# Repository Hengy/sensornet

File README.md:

SensorNet
-----------------------------------------------

SensorNet is a wireless network optimised for small data transfers that are typical of sensor and automation devices. Where the 802.11 standard (WiFi) is meant for large data streams, networking, etc. - with the overhead that comes with it - Sensornet is optimised for the inherently small data needed for sensors and automation control.

The data requirements of the typical sensor is from 1 bit (open/closed) to 24 bits (8-bit representation of a colour). Automation has similar requirements - from 1 bit (on/off) control, to 36 bits (12-bit PWM control of a RGB light).

Sensornet provides a common API for multiple microcontroller architectures, allowing simple transfer and management of sensor and automation control data, as well as a web-based interface centred around the inexpensive, but powerful Raspberry Pi platform.

Using the SensorNet libraries and templates, rapid development of SensorNet compatible sensors and automation controls is possible in as little as a few hours, while access to advanced features allow for complex, smart devices with advanced functionality.

iPhone App
Two good friends of mine developed an iPhone App for SensorNet. It can be found here: https://github.com/Qblack/SensorNet

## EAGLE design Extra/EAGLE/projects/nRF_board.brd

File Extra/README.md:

Extras
-----------------------------------------------

These are extras that were made during the development of SensorNet, mostly out of necessity.

The Temp Control folder contains a program to self regulate the RPis temperature using a fan. The fan speed is regulated using a PWM signal.

The EAGLE folder contains a PCB design for an interface board for the nRF24L01+. The board includes an optional 3.33v regulator, power LED, and reservoir capacitors. The reservoir capacitors are necessary when using a small microcontroller and a nRF24L01+ with a LNA. The power draw when switching to TX mode may be too much for the microcontroller. Reservoir capacitors fix this problem in most cases.

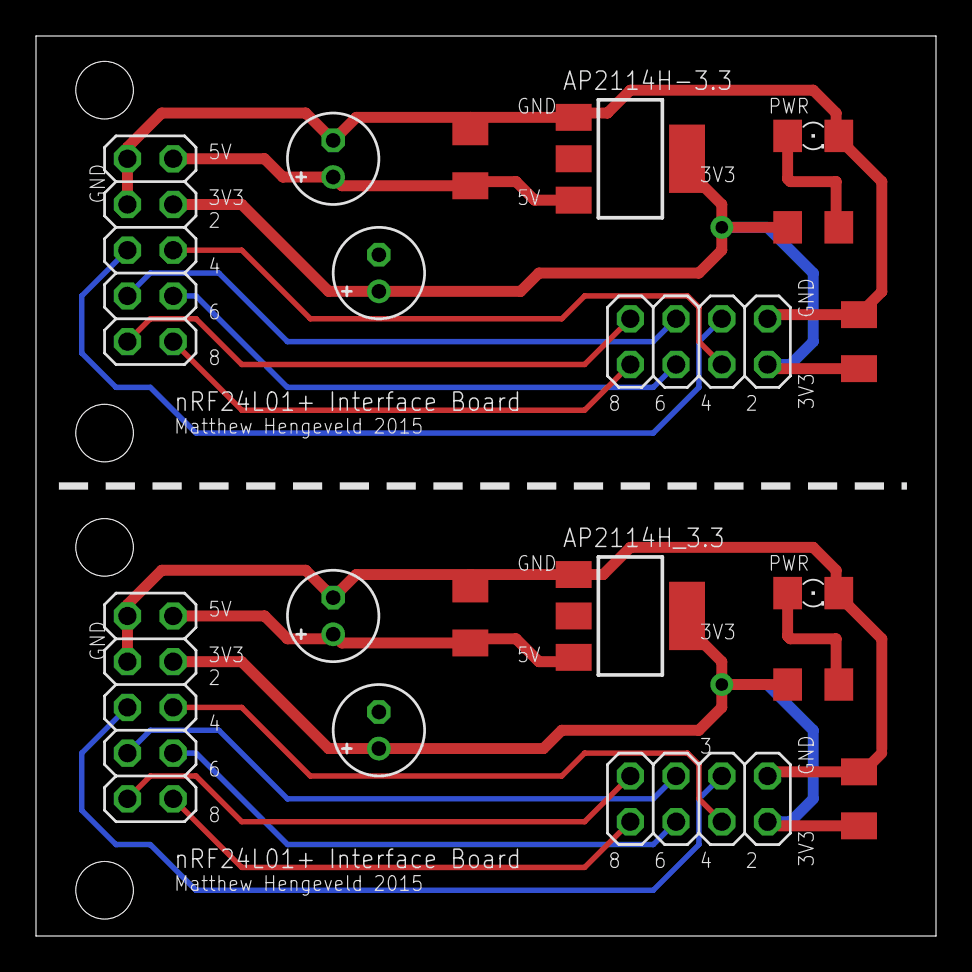
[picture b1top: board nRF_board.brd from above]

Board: 2 copper layers, 50.0 x 50.0 mm, 18 parts (0 on the bottom side), 17 nets.

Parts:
AP2114H-3.3, AP2114H_3.3: LD117AS28TR; SOT223
C1, C2, C5, C6: 0.1uF; C1206K
C3, C7: 10uF; E2-5
C4, C8: 4.7uF; E2-5
JP1, JP4: 2X05
JP2, JP3: 2X04
LED1_GREEN, LED1_GREEN1: 1206
R1, R2: 180R; R1206

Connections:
+3V3: AP2114H-3.3.4, AP2114H_3.3.4, C2.1, C3.+, C6.1, C7.+, JP1.7, JP2.7, JP3.7, JP4.7, R1.1, R2.1
+5V: AP2114H-3.3.3, AP2114H_3.3.3, C1.1, C4.+, C5.1, C8.+, JP1.9, JP4.9
GND: AP2114H-3.3.1, AP2114H_3.3.1, C1.2, C2.2, C3.-, C4.-, C5.2, C6.2, C7.-, C8.-, JP1.8, JP1.10, JP2.8, JP3.8, JP4.8, JP4.10, LED1_GREEN.C, LED1_GREEN1.C
unnamed: LED1_GREEN1.A, R2.2
unnamed: JP1.5, JP2.5
unnamed: LED1_GREEN.A, R1.2
unnamed: JP1.3, JP2.3
unnamed: JP1.1, JP2.1
unnamed: JP1.6, JP2.6
unnamed: JP1.4, JP2.4
unnamed: JP1.2, JP2.2
unnamed: JP3.5, JP4.5
unnamed: JP3.3, JP4.3
unnamed: JP3.1, JP4.1
unnamed: JP3.6, JP4.6
unnamed: JP3.4, JP4.4
unnamed: JP3.2, JP4.2

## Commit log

2014-09-11 Upload Website
    Uploaded started website concept.
2014-09-12 Upload MPLAB X files
2014-09-13 Added Reference Documents
2014-09-14 Corrs and Mods to files
    Added definition of CSN pin to PIC code
    Corrected CE pin to CSN pin
    Modified Arduino RX code to receive PIC TX
2014-09-14 Odd docs
    gitignore for Aptana .metedata folder
2014-09-15 Added reference to list
2014-09-15 Added pinout diagram to PIC18 main.c
2014-09-16 Added Arduino Files
2014-09-16 PIC code updated
2014-09-17 Deleted old project
    deleted old mplabx project under nRF_TX
2014-09-17 Update references
2014-09-17 PIC and Arduino code updated
2014-09-18 Arduino SPI, getSTATUS() working
2014-09-18 MSO Screen Captures
2014-09-19 PIC, Arduino code; MSO Screens
    Arduino SPI is confirmed working. PIC SPI is not confirmed, but scope
    says working. No working wireless communications.
2014-09-22 PIC, Arduino code
    wireless not working
2014-09-22 PIC, Arduino code
2014-09-24 New PIC code
    Rewriting PIC code
2014-09-24 PIC code
    TX not working
2014-09-24 PIC code - Transmit working!
    PIC transmits, IRQ pin fires, but PIC also spews out a bunch of garbage
    as well. Could be a reset - garbage contains some bytes that look like
    config func...
2014-09-25 PIC code - Transmit working, timing
    Working on lowering SPI timing
2014-09-25 PIC code - working, timing - 500KHz SPI
    timing is set for SPI speed of 500KHz
2014-09-25 Arduino code - WIRELESS WORKS!
    wireless link works - Arduino SPI mode unknown.. (SPI was the problem)
2014-09-25 PIC & Arduino - RX, TX code done
2014-09-26 PIC, Arduino code
    PIC - faster SPI (2MHz), RX code
    Arduino - RX Interrupts, TX code
2014-09-29 Auto Ack code
    Auto Ack not working
2014-09-29 Auto Ack code
    Auto Ack on TX side appears to work; RX side does not send Ack
2014-09-29 Arduino INT++ code
2014-09-30 PIC code
    No change
2014-09-30 dynamic payload
    problems with interrupts
2014-09-30 Revert "PIC & Arduino - RX, TX code done"
    This reverts commit ee72d6f622911c31390f05f9047e60168b804fe3.
    Conflicts:
    Arduino/nRF_RX/nRF_RX.ino
    MPLAB X/nRF24_RX.X/main.c
    MPLAB X/nRF24_RX.X/nbproject/Makefile-genesis.properties
    MPLAB X/nRF_TX/nRF24_TX.X/main.c
2014-09-30 Revert "PIC, Arduino code"
    This reverts commit 015c358bb45e253f8072ad9c0b4c1d947bb1604c.
    Conflicts:
    Arduino/nRF_RX/nRF_RX.ino
    Arduino/nRF_RX_INT/nRF_RX_INT.ino
    MPLAB X/nRF24_RX.X/main.c
    MPLAB X/nRF24_RX.X/nbproject/Makefile-genesis.properties
2014-09-30 Revert
2014-09-30 Deleted odd files
2014-09-30 Arduino Interrupts;
2014-09-30 PIC, Arduino - Dynamic payload
    dynamic payload working
2014-09-30 Dynamic payload - up to 16 bytes
    >15 bytes still sketchy - smaller Arduino loop seems to help to a point
2014-10-01 Arduino, PIC - 4MHz SPI
    Dynamic payload working - SPI speed must be > 500KHz to successfully
    transfer > 16 bytes
2014-10-01 PIC - starting interrupts
    MSSP1 transfer interrupt
    PORTB interrupt-on-change
2014-10-01 PIC interrupts; specify SPI speed
    IRQ changed to RB4; SPI data transmission complete flag instead of
    delay.
    Specify SPI speed using spiConfig argument, _XTAL_FREQ, general formula
    Working on IRQ interrupt using PORTB io change interrupts
2014-10-01 PIC all interrupts
    does not work
2014-10-02 PIC interrupts
    interrupts working
2014-10-02 Starting Auto Ack code
2014-10-03 PIC, Arduino - Auto Ack code working
2014-10-06 Started Arduino nRFSN library
2014-10-06 Arduino nRFSN library
2014-10-09 nRFSN Arduino library
2014-10-09 Arduino nRFSN library
    NOT working
2014-10-14 Arduino nRFSN library - working
2014-10-15 Arduino nRFSN Library
    working; added nRFSNCommands header file
2014-10-15 Arduino nRFSN Library & Template
    Library working, finished; template - no sync()
2014-10-15 Arduino Template
2014-10-15 Deleted old files
2014-10-16 PIC nRFSN Library
2014-10-16 PIC nRFSN Library
    PIC library now .c file
    compiles using #include <nRFSN/nRFSN.h>
    and folder in project properties "include directories"
2014-10-17 Library stuff
2014-10-17 Arduino, PIC libraries
    PIC: C "library" - must reference nRFSN project, took out initial init
    pin settings and SPI speed, added setSPIFreq function
    Arduino: C++ library
    TO DO: mod Arduino library - init(), add setSPIFreq?
2014-10-30 Added spidev documentation to ref docs
2014-11-04 misc
2014-11-05 RPi nrf24 library - start
2014-11-06 RPi nRFSN library
2014-11-07 music...
2014-11-07 Reference Docs
2014-11-07 RPi nRFSN library
    RPi -> Arduino works (for first transmission only)
2014-11-14 RPi nRFSN library - MAX_RT interrupt tripping
2014-11-17 stuff
2014-11-18 RPi nRFSN library WORKS!!
    no MAX_RT interrupt. Fix was pipe 1 not having proper address.
2014-11-19 libraries
2014-11-22 Merge remote-tracking branch 'origin/master'
    Conflicts:
    Baxandall Tone Control.asc
    Baxandall Tone Control.op.raw
    Baxandall Tone Control.raw
2014-12-01 stuff
    stuff
2015-01-06 FInal Stuff
2015-01-10 Housekeeping
2015-01-11 CompleteLibraries
2015-01-12 Arduino Lib Complete
2015-01-12 nRF_Board
2015-01-14 Library modifications
2015-01-14 Depreciated configReg
2015-01-19 WebInterface
2015-01-20 line
2015-01-24 WeInterface
2015-01-29 WebInterfaceSVG
2015-01-31 WebInterface_Database
2015-02-01 Database
2015-02-01 SVG image
2015-02-01 svg images
2015-02-02 WebInterface_DatabaseStatus
2015-02-02 WebInterface_JS
2015-02-03 WebInterface_!important
2015-02-05 cleanup
2015-02-05 Revert "WebInterface"
    This reverts commit 0a783f887f8038a11d2655d73c0ba4498b166ba3.
2015-02-05 Revert "cleanup"
    This reverts commit fd4b7a3703f54e70b2d4c387485b25e5a6c60302.
2015-02-07 main program
2015-02-19 Loading Animation
2015-02-19 menuButton
2015-02-25 sine
2015-03-02 auto temp
2015-03-12 CH340 driver
2015-03-12 dht11
2015-03-12 Arduino Nano Pinout
2015-03-16 RPi nRFSN
2015-03-18 things
2015-03-20 poster
2015-03-20 Libraries WORK!
2015-03-25 Arduinos
2015-03-26 ArduinoRGB
2015-03-26 ArdinoONOFF
2015-03-26 ArduinoRGBHSL
2015-03-26 Arduino nRFSN Lib
2015-03-31 Cleanup
    Cleaned out all old code, files
2015-04-09 Final Report
2015-04-13 Final Report
    ToC
2015-04-15 nRF board and schematic
2015-04-16 Photos
2015-04-16 Final Report, schematics and photos
2015-04-21 Update readme for iPhone app
